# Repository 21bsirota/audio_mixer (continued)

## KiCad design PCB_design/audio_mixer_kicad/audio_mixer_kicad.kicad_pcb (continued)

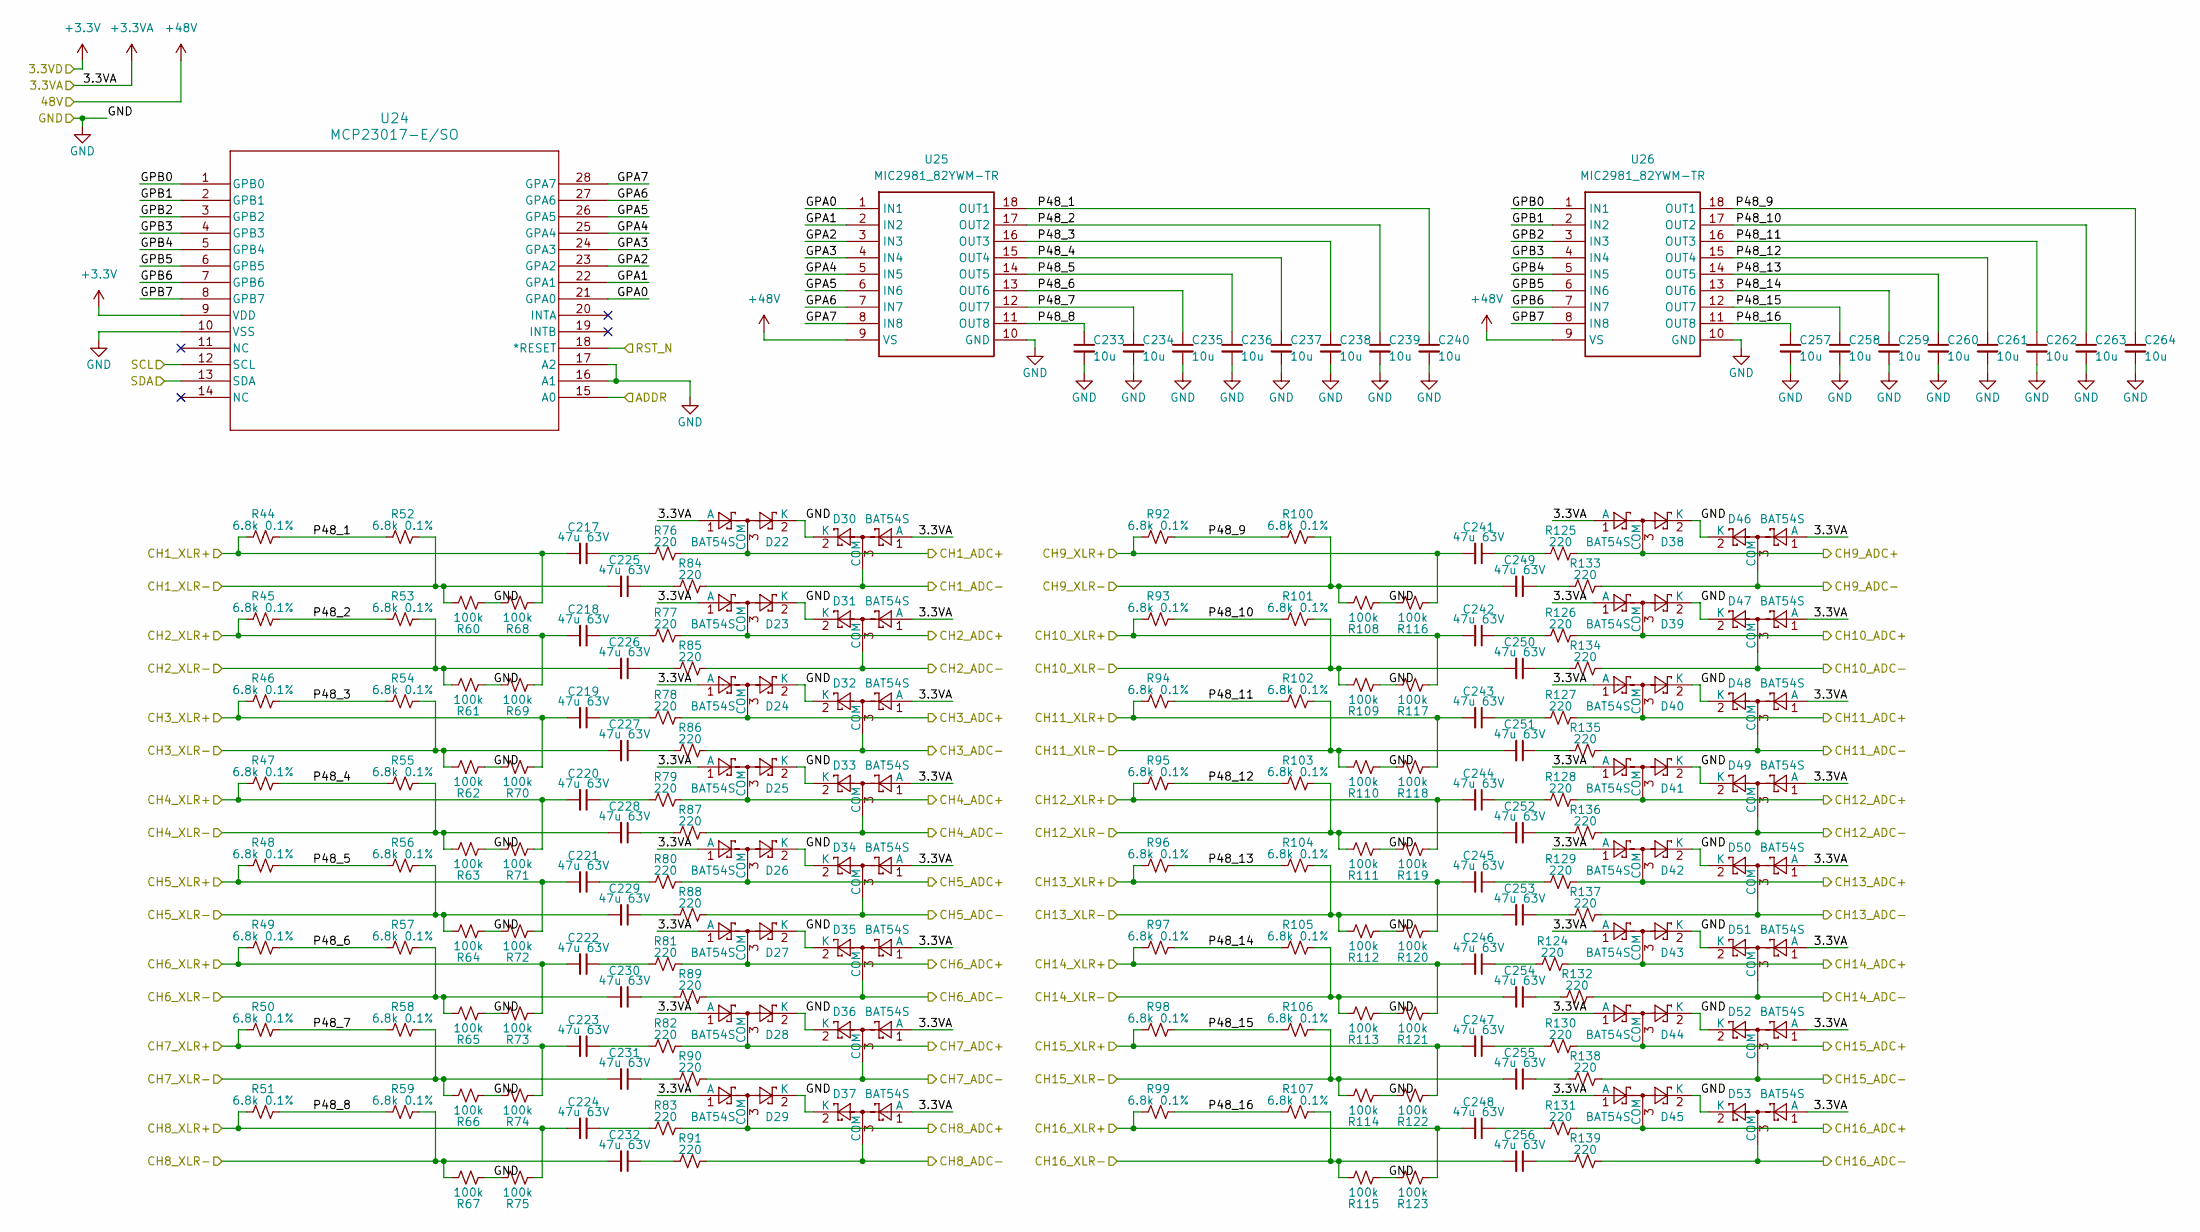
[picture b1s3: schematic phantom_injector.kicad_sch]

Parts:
C217, C218, C219, C220, C221, C222, C223, C224, C225, C226, C227, C228, C229, C230, C231, C232, C241, C242, C243, C244, C245, C246, C247, C248, C249, C250, C251, C252, C253, C254, C255, C256: 47u 63V; C_1206_3216Metric_Pad1.33x1.80mm_HandSolder
C233, C234, C235, C236, C237, C238, C239, C240, C257, C258, C259, C260, C261, C262, C263, C264: 10u; C_1206_3216Metric_Pad1.33x1.80mm_HandSolder
D22, D23, D24, D25, D26, D27, D28, D29, D30, D31, D32, D33, D34, D35, D36, D37, D38, D39, D40, D41, D42, D43, D44, D45, D46, D47, D48, D49, D50, D51, D52, D53: BAT54S; SOT-23
R44, R45, R46, R47, R48, R49, R50, R51, R52, R53, R54, R55, R56, R57, R58, R59, R92, R93, R94, R95, R96, R97, R98, R99, R100, R101, R102, R103, R104, R105, R106, R107: 6.8k 0.1%; R_1206_3216Metric_Pad1.30x1.75mm_HandSolder
R60, R61, R62, R63, R64, R65, R66, R67, R68, R69, R70, R71, R72, R73, R74, R75, R108, R109, R110, R111, R112, R113, R114, R115, R116, R117, R118, R119, R120, R121, R122, R123: 100k; R_1206_3216Metric_Pad1.30x1.75mm_HandSolder
R76, R77, R78, R79, R80, R81, R82, R83, R84, R85, R86, R87, R88, R89, R90, R91, R124, R125, R126, R127, R128, R129, R130, R131, R132, R133, R134, R135, R136, R137, R138, R139: 220; R_1206_3216Metric_Pad1.30x1.75mm_HandSolder
U24: MCP23017-E/SO; SOIC28-W_MC_MCH
U25, U26: MIC2981_82YWM-TR; SOIC127P1031X262-18N; Mouser Part Number 998-MIC2981/82YWMTR

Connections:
+3.3V: U24.9 (VDD); also elsewhere on the board
+3.3VA: D22.1 (A), D23.1 (A), D24.1 (A), D25.1 (A), D26.1 (A), D27.1 (A), D28.1 (A), D29.1 (A), D30.1 (A), D31.1 (A), D32.1 (A), D33.1 (A), D34.1 (A), D35.1 (A), D36.1 (A), D37.1 (A), D38.1 (A), D39.1 (A), D40.1 (A), D41.1 (A), D42.1 (A), D43.1 (A), D44.1 (A), D45.1 (A), D46.1 (A), D47.1 (A), D48.1 (A), D49.1 (A), D50.1 (A), D51.1 (A), D52.1 (A), D53.1 (A); also elsewhere on the board
+48V: U25.9 (VS), U26.9 (VS); also elsewhere on the board
/CH1_ADC+: D22.3 (COM), R76.2; also elsewhere on the board
/CH1_ADC-: D30.3 (COM), R84.2; also elsewhere on the board
/CH1_XLR+: C217.2, R44.1, R68.2; also elsewhere on the board
/CH1_XLR-: C225.2, R52.2, R60.1; also elsewhere on the board
/CH2_ADC+: D23.3 (COM), R77.2; also elsewhere on the board
/CH2_ADC-: D31.3 (COM), R85.2; also elsewhere on the board
/CH2_XLR+: C218.2, R45.1, R69.2; also elsewhere on the board
/CH2_XLR-: C226.2, R53.2, R61.1; also elsewhere on the board
/CH3_ADC+: D24.3 (COM), R78.2; also elsewhere on the board
/CH3_ADC-: D32.3 (COM), R86.2; also elsewhere on the board
/CH3_XLR+: C219.2, R46.1, R70.2; also elsewhere on the board
/CH3_XLR-: C227.2, R54.2, R62.1; also elsewhere on the board
/CH4_ADC+: D25.3 (COM), R79.2; also elsewhere on the board
/CH4_ADC-: D33.3 (COM), R87.2; also elsewhere on the board
/CH4_XLR+: C220.2, R47.1, R71.2; also elsewhere on the board
/CH4_XLR-: C228.2, R55.2, R63.1; also elsewhere on the board
/CH5_ADC+: D26.3 (COM), R80.2; also elsewhere on the board
/CH5_ADC-: D34.3 (COM), R88.2; also elsewhere on the board
/CH5_XLR+: C221.2, R48.1, R72.2; also elsewhere on the board
/CH5_XLR-: C229.2, R56.2, R64.1; also elsewhere on the board
/CH6_ADC+: D27.3 (COM), R81.2; also elsewhere on the board
/CH6_ADC-: D35.3 (COM), R89.2; also elsewhere on the board
/CH6_XLR+: C222.2, R49.1, R73.2; also elsewhere on the board
/CH6_XLR-: C230.2, R57.2, R65.1; also elsewhere on the board
/CH7_ADC+: D28.3 (COM), R82.2; also elsewhere on the board
/CH7_ADC-: D36.3 (COM), R90.2; also elsewhere on the board
/CH7_XLR+: C223.2, R50.1, R74.2; also elsewhere on the board
/CH7_XLR-: C231.2, R58.2, R66.1; also elsewhere on the board
/CH8_ADC+: D29.3 (COM), R83.2; also elsewhere on the board
/CH8_ADC-: D37.3 (COM), R91.2; also elsewhere on the board
/CH8_XLR+: C224.2, R51.1, R75.2; also elsewhere on the board
/CH8_XLR-: C232.2, R59.2, R67.1; also elsewhere on the board
/CH9_ADC+: D38.3 (COM), R125.2; also elsewhere on the board
/CH9_ADC-: D46.3 (COM), R133.2; also elsewhere on the board
/CH9_XLR+: C241.2, R92.1, R116.2; also elsewhere on the board
/CH9_XLR-: C249.2, R100.2, R108.1; also elsewhere on the board
/CH10_ADC+: D39.3 (COM), R126.2; also elsewhere on the board
/CH10_ADC-: D47.3 (COM), R134.2; also elsewhere on the board
/CH10_XLR+: C242.2, R93.1, R117.2; also elsewhere on the board
/CH10_XLR-: C250.2, R101.2, R109.1; also elsewhere on the board
/CH11_ADC+: D40.3 (COM), R127.2; also elsewhere on the board
/CH11_ADC-: D48.3 (COM), R135.2; also elsewhere on the board
/CH11_XLR+: C243.2, R94.1, R118.2; also elsewhere on the board
/CH11_XLR-: C251.2, R102.2, R110.1; also elsewhere on the board
/CH12_ADC+: D41.3 (COM), R128.2; also elsewhere on the board
/CH12_ADC-: D49.3 (COM), R136.2; also elsewhere on the board
/CH12_XLR+: C244.2, R95.1, R119.2; also elsewhere on the board
/CH12_XLR-: C252.2, R103.2, R111.1; also elsewhere on the board
/CH13_ADC+: D42.3 (COM), R129.2; also elsewhere on the board
/CH13_ADC-: D50.3 (COM), R137.2; also elsewhere on the board
/CH13_XLR+: C245.2, R96.1, R120.2; also elsewhere on the board
/CH13_XLR-: C253.2, R104.2, R112.1; also elsewhere on the board
/CH14_ADC+: D43.3 (COM), R124.2; also elsewhere on the board
/CH14_ADC-: D51.3 (COM), R132.2; also elsewhere on the board
/CH14_XLR+: C246.2, R97.1, R121.2; also elsewhere on the board
/CH14_XLR-: C254.2, R105.2, R113.1; also elsewhere on the board
/CH15_ADC+: D44.3 (COM), R130.2; also elsewhere on the board
/CH15_ADC-: D52.3 (COM), R138.2; also elsewhere on the board
/CH15_XLR+: C247.2, R98.1, R122.2; also elsewhere on the board
/CH15_XLR-: C255.2, R106.2, R114.1; also elsewhere on the board
/CH16_ADC+: D45.3 (COM), R131.2; also elsewhere on the board
/CH16_ADC-: D53.3 (COM), R139.2; also elsewhere on the board
/CH16_XLR+: C248.2, R99.1, R123.2; also elsewhere on the board
/CH16_XLR-: C256.2, R107.2, R115.1; also elsewhere on the board
/I2C1_SCL: U24.12 (SCL); also elsewhere on the board
/I2C1_SDA: U24.13 (SDA); also elsewhere on the board
/Phantom Injector 0/GPA0: U24.21 (GPA0), U25.1 (IN1)
/Phantom Injector 0/GPA1: U24.22 (GPA1), U25.2 (IN2)
/Phantom Injector 0/GPA2: U24.23 (GPA2), U25.3 (IN3)
/Phantom Injector 0/GPA3: U24.24 (GPA3), U25.4 (IN4)
/Phantom Injector 0/GPA4: U24.25 (GPA4), U25.5 (IN5)
/Phantom Injector 0/GPA5: U24.26 (GPA5), U25.6 (IN6)
/Phantom Injector 0/GPA6: U24.27 (GPA6), U25.7 (IN7)
/Phantom Injector 0/GPA7: U24.28 (GPA7), U25.8 (IN8)
/Phantom Injector 0/GPB0: U24.1 (GPB0), U26.1 (IN1)
/Phantom Injector 0/GPB1: U24.2 (GPB1), U26.2 (IN2)
/Phantom Injector 0/GPB2: U24.3 (GPB2), U26.3 (IN3)
/Phantom Injector 0/GPB3: U24.4 (GPB3), U26.4 (IN4)
/Phantom Injector 0/GPB4: U24.5 (GPB4), U26.5 (IN5)
/Phantom Injector 0/GPB5: U24.6 (GPB5), U26.6 (IN6)
/Phantom Injector 0/GPB6: U24.7 (GPB6), U26.7 (IN7)
/Phantom Injector 0/GPB7: U24.8 (GPB7), U26.8 (IN8)
/Phantom Injector 0/P48_1: C240.1, R44.2, R52.1, U25.18 (OUT1)
/Phantom Injector 0/P48_2: C239.1, R45.2, R53.1, U25.17 (OUT2)
/Phantom Injector 0/P48_3: C238.1, R46.2, R54.1, U25.16 (OUT3)
/Phantom Injector 0/P48_4: C237.1, R47.2, R55.1, U25.15 (OUT4)
/Phantom Injector 0/P48_5: C236.1, R48.2, R56.1, U25.14 (OUT5)
/Phantom Injector 0/P48_6: C235.1, R49.2, R57.1, U25.13 (OUT6)
/Phantom Injector 0/P48_7: C234.1, R50.2, R58.1, U25.12 (OUT7)
/Phantom Injector 0/P48_8: C233.1, R51.2, R59.1, U25.11 (OUT8)
/Phantom Injector 0/P48_9: C264.1, R92.2, R100.1, U26.18 (OUT1)
/Phantom Injector 0/P48_10: C263.1, R93.2, R101.1, U26.17 (OUT2)
/Phantom Injector 0/P48_11: C262.1, R94.2, R102.1, U26.16 (OUT3)
/Phantom Injector 0/P48_12: C261.1, R95.2, R103.1, U26.15 (OUT4)
/Phantom Injector 0/P48_13: C260.1, R96.2, R104.1, U26.14 (OUT5)
/Phantom Injector 0/P48_14: C259.1, R97.2, R105.1, U26.13 (OUT6)
/Phantom Injector 0/P48_15: C258.1, R98.2, R106.1, U26.12 (OUT7)
/Phantom Injector 0/P48_16: C257.1, R99.2, R107.1, U26.11 (OUT8)
/RST_N: U24.18 (*RESET); also elsewhere on the board
GND: C233.2, C234.2, C235.2, C236.2, C237.2, C238.2, C239.2, C240.2, C257.2, C258.2, C259.2, C260.2, C261.2, C262.2, C263.2, C264.2, D22.2 (K), D23.2 (K), D24.2 (K), D25.2 (K), D26.2 (K), D27.2 (K), D28.2 (K), D29.2 (K), D30.2 (K), D31.2 (K), D32.2 (K), D33.2 (K), D34.2 (K), D35.2 (K), D36.2 (K), D37.2 (K), D38.2 (K), D39.2 (K), D40.2 (K), D41.2 (K), D42.2 (K), D43.2 (K), D44.2 (K), D45.2 (K), D46.2 (K), D47.2 (K), D48.2 (K), D49.2 (K), D50.2 (K), D51.2 (K), D52.2 (K), D53.2 (K), R60.2, R61.2, R62.2, R63.2, R64.2, R65.2, R66.2, R67.2, R68.1, R69.1, R70.1, R71.1, R72.1, R73.1, R74.1, R75.1, R108.2, R109.2, R110.2, R111.2, R112.2, R113.2, R114.2, R115.2, R116.1, R117.1, R118.1, R119.1, R120.1, R121.1, R122.1, R123.1, U24.10 (VSS), U24.15 (A0), U24.16 (A1), U24.17 (A2), U25.10 (GND), U26.10 (GND); also elsewhere on the board
unnamed: C217.1, R76.1
unnamed: C218.1, R77.1
unnamed: C219.1, R78.1
unnamed: C220.1, R79.1
unnamed: C221.1, R80.1
unnamed: C222.1, R81.1
unnamed: C223.1, R82.1
unnamed: C224.1, R83.1
unnamed: C225.1, R84.1
unnamed: C226.1, R85.1
unnamed: C227.1, R86.1
unnamed: C228.1, R87.1
unnamed: C229.1, R88.1
unnamed: C230.1, R89.1
unnamed: C231.1, R90.1
unnamed: C232.1, R91.1
unnamed: C241.1, R125.1
unnamed: C242.1, R126.1
unnamed: C243.1, R127.1
unnamed: C244.1, R128.1
unnamed: C245.1, R129.1
unnamed: C246.1, R124.1
unnamed: C247.1, R130.1
unnamed: C248.1, R131.1
unnamed: C249.1, R133.1
unnamed: C250.1, R134.1
unnamed: C251.1, R135.1
unnamed: C252.1, R136.1
unnamed: C253.1, R137.1
unnamed: C254.1, R132.1
unnamed: C255.1, R138.1
unnamed: C256.1, R139.1

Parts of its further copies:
C265, C266, C267, C268, C269, C270, C271, C272, C273, C274, C275, C276, C277, C278, C279, C280, C289, C290, C291, C292, C293, C294, C295, C296, C297, C298, C299, C300, C301, C302, C303, C304: 47u 63V; C_1206_3216Metric_Pad1.33x1.80mm_HandSolder
C281, C282, C283, C284, C285, C286, C287, C288, C305, C306, C307, C308, C309, C310, C311, C312: 10u; C_1206_3216Metric_Pad1.33x1.80mm_HandSolder
D54, D55, D56, D57, D58, D59, D60, D61, D62, D63, D64, D65, D66, D67, D68, D69, D70, D71, D72, D73, D74, D75, D76, D77, D78, D79, D80, D81, D82, D83, D84, D85: BAT54S; SOT-23
R140, R141, R142, R143, R144, R145, R146, R147, R148, R149, R150, R151, R152, R153, R154, R155, R188, R189, R190, R191, R192, R193, R194, R195, R196, R197, R198, R199, R200, R201, R202, R203: 6.8k 0.1%; R_1206_3216Metric_Pad1.30x1.75mm_HandSolder
R156, R157, R158, R159, R160, R161, R162, R163, R164, R165, R166, R167, R168, R169, R170, R171, R204, R205, R206, R207, R208, R209, R210, R211, R212, R213, R214, R215, R216, R217, R218, R219: 100k; R_1206_3216Metric_Pad1.30x1.75mm_HandSolder
R172, R173, R174, R175, R176, R177, R178, R179, R180, R181, R182, R183, R184, R185, R186, R187, R220, R221, R222, R223, R224, R225, R226, R227, R228, R229, R230, R231, R232, R233, R234, R235: 220; R_1206_3216Metric_Pad1.30x1.75mm_HandSolder
U27: MCP23017-E/SO; SOIC28-W_MC_MCH
U28, U29: MIC2981_82YWM-TR; SOIC127P1031X262-18N; Mouser Part Number 998-MIC2981/82YWMTR

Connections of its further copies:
+3.3V: U27.9 (VDD), U27.15 (A0); also elsewhere on the board
+3.3VA: D54.1 (A), D55.1 (A), D56.1 (A), D57.1 (A), D58.1 (A), D59.1 (A), D60.1 (A), D61.1 (A), D62.1 (A), D63.1 (A), D64.1 (A), D65.1 (A), D66.1 (A), D67.1 (A), D68.1 (A), D69.1 (A), D70.1 (A), D71.1 (A), D72.1 (A), D73.1 (A), D74.1 (A), D75.1 (A), D76.1 (A), D77.1 (A), D78.1 (A), D79.1 (A), D80.1 (A), D81.1 (A), D82.1 (A), D83.1 (A), D84.1 (A), D85.1 (A); also elsewhere on the board
+48V: U28.9 (VS), U29.9 (VS); also elsewhere on the board
/CH17_ADC+: D54.3 (COM), R172.2; also elsewhere on the board
/CH17_ADC-: D62.3 (COM), R180.2; also elsewhere on the board
/CH17_XLR+: C265.2, R140.1, R164.2; also elsewhere on the board
/CH17_XLR-: C273.2, R148.2, R156.1; also elsewhere on the board
/CH18_ADC+: D55.3 (COM), R173.2; also elsewhere on the board
/CH18_ADC-: D63.3 (COM), R181.2; also elsewhere on the board
/CH18_XLR+: C266.2, R141.1, R165.2; also elsewhere on the board
/CH18_XLR-: C274.2, R149.2, R157.1; also elsewhere on the board
/CH19_ADC+: D56.3 (COM), R174.2; also elsewhere on the board
/CH19_ADC-: D64.3 (COM), R182.2; also elsewhere on the board
/CH19_XLR+: C267.2, R142.1, R166.2; also elsewhere on the board
/CH19_XLR-: C275.2, R150.2, R158.1; also elsewhere on the board
/CH20_ADC+: D57.3 (COM), R175.2; also elsewhere on the board
/CH20_ADC-: D65.3 (COM), R183.2; also elsewhere on the board
/CH20_XLR+: C268.2, R143.1, R167.2; also elsewhere on the board
/CH20_XLR-: C276.2, R151.2, R159.1; also elsewhere on the board
/CH21_ADC+: D58.3 (COM), R176.2; also elsewhere on the board
/CH21_ADC-: D66.3 (COM), R184.2; also elsewhere on the board
/CH21_XLR+: C269.2, R144.1, R168.2; also elsewhere on the board
/CH21_XLR-: C277.2, R152.2, R160.1; also elsewhere on the board
/CH22_ADC+: D59.3 (COM), R177.2; also elsewhere on the board
/CH22_ADC-: D67.3 (COM), R185.2; also elsewhere on the board
/CH22_XLR+: C270.2, R145.1, R169.2; also elsewhere on the board
/CH22_XLR-: C278.2, R153.2, R161.1; also elsewhere on the board
/CH23_ADC+: D60.3 (COM), R178.2; also elsewhere on the board
/CH23_ADC-: D68.3 (COM), R186.2; also elsewhere on the board
/CH23_XLR+: C271.2, R146.1, R170.2; also elsewhere on the board
/CH23_XLR-: C279.2, R154.2, R162.1; also elsewhere on the board
/CH24_ADC+: D61.3 (COM), R179.2; also elsewhere on the board
/CH24_ADC-: D69.3 (COM), R187.2; also elsewhere on the board
/CH24_XLR+: C272.2, R147.1, R171.2; also elsewhere on the board
/CH24_XLR-: C280.2, R155.2, R163.1; also elsewhere on the board
/CH25_ADC+: D70.3 (COM), R221.2; also elsewhere on the board
/CH25_ADC-: D78.3 (COM), R229.2; also elsewhere on the board
/CH25_XLR+: C289.2, R188.1, R212.2; also elsewhere on the board
/CH25_XLR-: C297.2, R196.2, R204.1; also elsewhere on the board
/CH26_ADC+: D71.3 (COM), R222.2; also elsewhere on the board
/CH26_ADC-: D79.3 (COM), R230.2; also elsewhere on the board
/CH26_XLR+: C290.2, R189.1, R213.2; also elsewhere on the board
/CH26_XLR-: C298.2, R197.2, R205.1; also elsewhere on the board
/CH27_ADC+: D72.3 (COM), R223.2; also elsewhere on the board
/CH27_ADC-: D80.3 (COM), R231.2; also elsewhere on the board
/CH27_XLR+: C291.2, R190.1, R214.2; also elsewhere on the board
/CH27_XLR-: C299.2, R198.2, R206.1; also elsewhere on the board
/CH28_ADC+: D73.3 (COM), R224.2; also elsewhere on the board
/CH28_ADC-: D81.3 (COM), R232.2; also elsewhere on the board
/CH28_XLR+: C292.2, R191.1, R215.2; also elsewhere on the board
/CH28_XLR-: C300.2, R199.2, R207.1; also elsewhere on the board
/CH29_ADC+: D74.3 (COM), R225.2; also elsewhere on the board
/CH29_ADC-: D82.3 (COM), R233.2; also elsewhere on the board
/CH29_XLR+: C293.2, R192.1, R216.2; also elsewhere on the board
/CH29_XLR-: C301.2, R200.2, R208.1; also elsewhere on the board
/CH30_ADC+: D75.3 (COM), R220.2; also elsewhere on the board
/CH30_ADC-: D83.3 (COM), R228.2; also elsewhere on the board
/CH30_XLR+: C294.2, R193.1, R217.2; also elsewhere on the board
/CH30_XLR-: C302.2, R201.2, R209.1; also elsewhere on the board
/CH31_ADC+: D76.3 (COM), R226.2; also elsewhere on the board
/CH31_ADC-: D84.3 (COM), R234.2; also elsewhere on the board
/CH31_XLR+: C295.2, R194.1, R218.2; also elsewhere on the board
/CH31_XLR-: C303.2, R202.2, R210.1; also elsewhere on the board
/CH32_ADC+: D77.3 (COM), R227.2; also elsewhere on the board
/CH32_ADC-: D85.3 (COM), R235.2; also elsewhere on the board
/CH32_XLR+: C296.2, R195.1, R219.2; also elsewhere on the board
/CH32_XLR-: C304.2, R203.2, R211.1; also elsewhere on the board
/I2C0_SCL: U27.12 (SCL); also elsewhere on the board
/I2C0_SDA: U27.13 (SDA); also elsewhere on the board
/Phantom Injector 1/GPA0: U27.21 (GPA0), U28.1 (IN1)
/Phantom Injector 1/GPA1: U27.22 (GPA1), U28.2 (IN2)
/Phantom Injector 1/GPA2: U27.23 (GPA2), U28.3 (IN3)
/Phantom Injector 1/GPA3: U27.24 (GPA3), U28.4 (IN4)
/Phantom Injector 1/GPA4: U27.25 (GPA4), U28.5 (IN5)
/Phantom Injector 1/GPA5: U27.26 (GPA5), U28.6 (IN6)
/Phantom Injector 1/GPA6: U27.27 (GPA6), U28.7 (IN7)
/Phantom Injector 1/GPA7: U27.28 (GPA7), U28.8 (IN8)
/Phantom Injector 1/GPB0: U27.1 (GPB0), U29.1 (IN1)
/Phantom Injector 1/GPB1: U27.2 (GPB1), U29.2 (IN2)
/Phantom Injector 1/GPB2: U27.3 (GPB2), U29.3 (IN3)
/Phantom Injector 1/GPB3: U27.4 (GPB3), U29.4 (IN4)
/Phantom Injector 1/GPB4: U27.5 (GPB4), U29.5 (IN5)
/Phantom Injector 1/GPB5: U27.6 (GPB5), U29.6 (IN6)
/Phantom Injector 1/GPB6: U27.7 (GPB6), U29.7 (IN7)
/Phantom Injector 1/GPB7: U27.8 (GPB7), U29.8 (IN8)
/Phantom Injector 1/P48_1: C288.1, R140.2, R148.1, U28.18 (OUT1)
/Phantom Injector 1/P48_2: C287.1, R141.2, R149.1, U28.17 (OUT2)
/Phantom Injector 1/P48_3: C286.1, R142.2, R150.1, U28.16 (OUT3)
/Phantom Injector 1/P48_4: C285.1, R143.2, R151.1, U28.15 (OUT4)
/Phantom Injector 1/P48_5: C284.1, R144.2, R152.1, U28.14 (OUT5)
/Phantom Injector 1/P48_6: C283.1, R145.2, R153.1, U28.13 (OUT6)
/Phantom Injector 1/P48_7: C282.1, R146.2, R154.1, U28.12 (OUT7)
/Phantom Injector 1/P48_8: C281.1, R147.2, R155.1, U28.11 (OUT8)
/Phantom Injector 1/P48_9: C312.1, R188.2, R196.1, U29.18 (OUT1)
/Phantom Injector 1/P48_10: C311.1, R189.2, R197.1, U29.17 (OUT2)
/Phantom Injector 1/P48_11: C310.1, R190.2, R198.1, U29.16 (OUT3)
/Phantom Injector 1/P48_12: C309.1, R191.2, R199.1, U29.15 (OUT4)
/Phantom Injector 1/P48_13: C308.1, R192.2, R200.1, U29.14 (OUT5)
/Phantom Injector 1/P48_14: C307.1, R193.2, R201.1, U29.13 (OUT6)
/Phantom Injector 1/P48_15: C306.1, R194.2, R202.1, U29.12 (OUT7)
/Phantom Injector 1/P48_16: C305.1, R195.2, R203.1, U29.11 (OUT8)
/RST_N: U27.18 (*RESET); also elsewhere on the board
GND: C281.2, C282.2, C283.2, C284.2, C285.2, C286.2, C287.2, C288.2, C305.2, C306.2, C307.2, C308.2, C309.2, C310.2, C311.2, C312.2, D54.2 (K), D55.2 (K), D56.2 (K), D57.2 (K), D58.2 (K), D59.2 (K), D60.2 (K), D61.2 (K), D62.2 (K), D63.2 (K), D64.2 (K), D65.2 (K), D66.2 (K), D67.2 (K), D68.2 (K), D69.2 (K), D70.2 (K), D71.2 (K), D72.2 (K), D73.2 (K), D74.2 (K), D75.2 (K), D76.2 (K), D77.2 (K), D78.2 (K), D79.2 (K), D80.2 (K), D81.2 (K), D82.2 (K), D83.2 (K), D84.2 (K), D85.2 (K), R156.2, R157.2, R158.2, R159.2, R160.2, R161.2, R162.2, R163.2, R164.1, R165.1, R166.1, R167.1, R168.1, R169.1, R170.1, R171.1, R204.2, R205.2, R206.2, R207.2, R208.2, R209.2, R210.2, R211.2, R212.1, R213.1, R214.1, R215.1, R216.1, R217.1, R218.1, R219.1, U27.10 (VSS), U27.16 (A1), U27.17 (A2), U28.10 (GND), U29.10 (GND); also elsewhere on the board
unnamed: C265.1, R172.1
unnamed: C266.1, R173.1
unnamed: C267.1, R174.1
unnamed: C268.1, R175.1
unnamed: C269.1, R176.1
unnamed: C270.1, R177.1
unnamed: C271.1, R178.1
unnamed: C272.1, R179.1
unnamed: C273.1, R180.1
unnamed: C274.1, R181.1
unnamed: C275.1, R182.1
unnamed: C276.1, R183.1
unnamed: C277.1, R184.1
unnamed: C278.1, R185.1
unnamed: C279.1, R186.1
unnamed: C280.1, R187.1
unnamed: C289.1, R221.1
unnamed: C290.1, R222.1
unnamed: C291.1, R223.1
unnamed: C292.1, R224.1
unnamed: C293.1, R225.1
unnamed: C294.1, R220.1
unnamed: C295.1, R226.1
unnamed: C296.1, R227.1
unnamed: C297.1, R229.1
unnamed: C298.1, R230.1
unnamed: C299.1, R231.1
unnamed: C300.1, R232.1
unnamed: C301.1, R233.1
unnamed: C302.1, R228.1
unnamed: C303.1, R234.1
unnamed: C304.1, R235.1

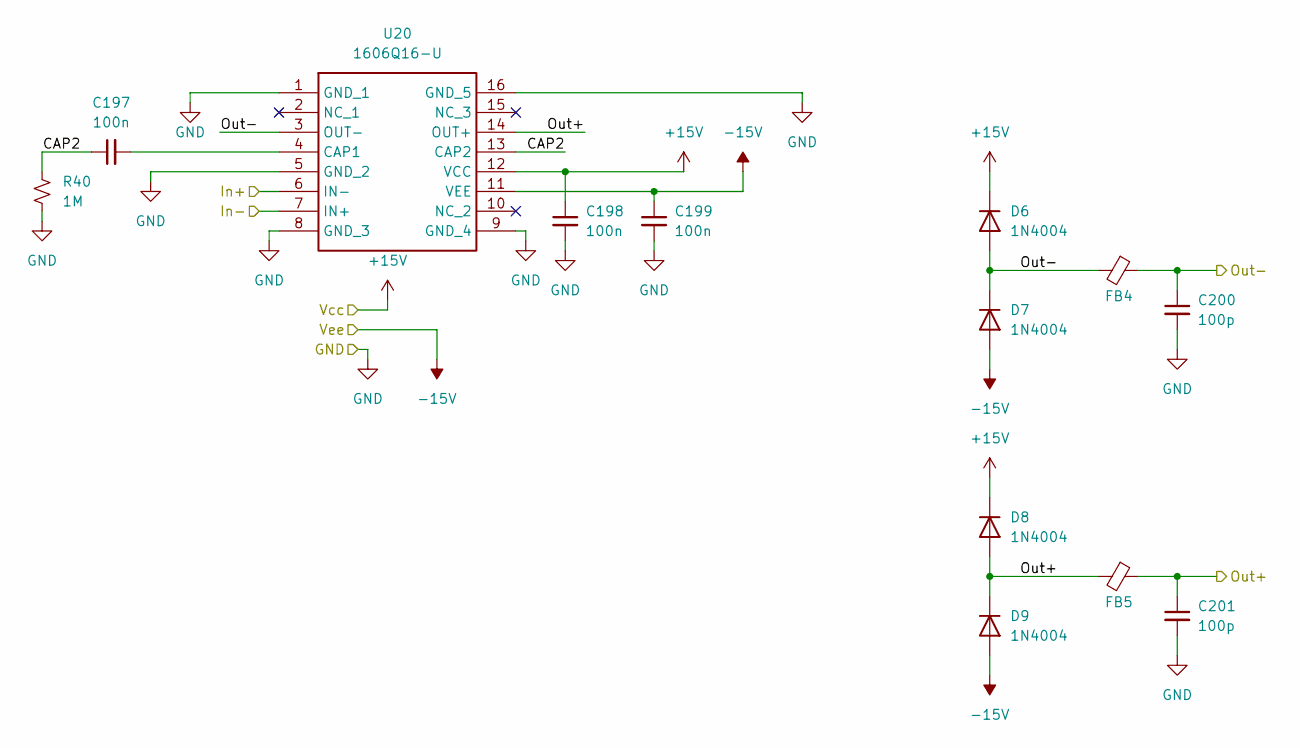
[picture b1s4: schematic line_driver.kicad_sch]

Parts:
C197, C198, C199: 100n; C_1206_3216Metric_Pad1.33x1.80mm_HandSolder
C200, C201: 100p; C_1206_3216Metric_Pad1.33x1.80mm_HandSolder
D6, D7, D8, D9: 1N4004; D_DO-41_SOD81_P10.16mm_Horizontal
FB4, FB5: FerriteBead_Small; L_1206_3216Metric_Pad1.22x1.90mm_HandSolder
R40: 1M; R_1206_3216Metric_Pad1.30x1.75mm_HandSolder
U20: 1606Q16-U; SOP64P600X175-16N; Mouser Part Number 887-1606Q16-U

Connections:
+15V: C198.1, D6.1 (K), D8.1 (K), U20.12 (VCC); also elsewhere on the board
-15V: C199.1, D7.2 (A), D9.2 (A), U20.11 (VEE); also elsewhere on the board
/DAC0/OUT1M: U20.7 (IN+); also elsewhere on the board
/DAC0/OUT1P: U20.6 (IN-); also elsewhere on the board
/LD0/CAP2: C197.1, R40.2, U20.13 (CAP2)
/LD0/Out+: C201.1, D8.2 (A), D9.1 (K), FB5.1, FB5.2, U20.14 (OUT+); also elsewhere on the board
/LD0/Out-: C200.1, D6.2 (A), D7.1 (K), FB4.1, FB4.2, U20.3 (OUT-); also elsewhere on the board
GND: C198.2, C199.2, C200.2, C201.2, R40.1, U20.1 (GND_1), U20.5 (GND_2), U20.8 (GND_3), U20.9 (GND_4), U20.16 (GND_5); also elsewhere on the board
unnamed: C197.2, U20.4 (CAP1)

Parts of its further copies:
C202, C203, C204, C207, C208, C209, C212, C213, C214: 100n; C_1206_3216Metric_Pad1.33x1.80mm_HandSolder
C205, C206, C210, C211, C215, C216: 100p; C_1206_3216Metric_Pad1.33x1.80mm_HandSolder
D10, D11, D12, D13, D14, D15, D16, D17, D18, D19, D20, D21: 1N4004; D_DO-41_SOD81_P10.16mm_Horizontal
FB6, FB7, FB8, FB9, FB10, FB11: FerriteBead_Small; L_1206_3216Metric_Pad1.22x1.90mm_HandSolder
R41, R42, R43: 1M; R_1206_3216Metric_Pad1.30x1.75mm_HandSolder
U21, U22, U23: 1606Q16-U; SOP64P600X175-16N; Mouser Part Number 887-1606Q16-U

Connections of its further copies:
+15V: C203.1, C208.1, C213.1, D10.1 (K), D12.1 (K), D14.1 (K), D16.1 (K), D18.1 (K), D20.1 (K), U21.12 (VCC), U22.12 (VCC), U23.12 (VCC); also elsewhere on the board
-15V: C204.1, C209.1, C214.1, D11.2 (A), D13.2 (A), D15.2 (A), D17.2 (A), D19.2 (A), D21.2 (A), U21.11 (VEE), U22.11 (VEE), U23.11 (VEE); also elsewhere on the board
/DAC0/OUT2M: U21.7 (IN+); also elsewhere on the board
/DAC0/OUT2P: U21.6 (IN-); also elsewhere on the board
/DAC1/OUT1M: U22.7 (IN+); also elsewhere on the board
/DAC1/OUT1P: U22.6 (IN-); also elsewhere on the board
/DAC1/OUT2M: U23.7 (IN+); also elsewhere on the board
/DAC1/OUT2P: U23.6 (IN-); also elsewhere on the board
/LD1/CAP2: C202.1, R41.2, U21.13 (CAP2)
/LD1/Out+: C206.1, D12.2 (A), D13.1 (K), FB7.1, FB7.2, U21.14 (OUT+); also elsewhere on the board
/LD1/Out-: C205.1, D10.2 (A), D11.1 (K), FB6.1, FB6.2, U21.3 (OUT-); also elsewhere on the board
/LD2/CAP2: C207.1, R42.2, U22.13 (CAP2)
/LD2/Out+: C211.1, D16.2 (A), D17.1 (K), FB9.1, FB9.2, U22.14 (OUT+); also elsewhere on the board
/LD2/Out-: C210.1, D14.2 (A), D15.1 (K), FB8.1, FB8.2, U22.3 (OUT-); also elsewhere on the board
/LD3/CAP2: C212.1, R43.2, U23.13 (CAP2)
/LD3/Out+: C216.1, D20.2 (A), D21.1 (K), FB11.1, FB11.2, U23.14 (OUT+); also elsewhere on the board
/LD3/Out-: C215.1, D18.2 (A), D19.1 (K), FB10.1, FB10.2, U23.3 (OUT-); also elsewhere on the board
GND: C203.2, C204.2, C205.2, C206.2, C208.2, C209.2, C210.2, C211.2, C213.2, C214.2, C215.2, C216.2, R41.1, R42.1, R43.1, U21.1 (GND_1), U21.5 (GND_2), U21.8 (GND_3), U21.9 (GND_4), U21.16 (GND_5), U22.1 (GND_1), U22.5 (GND_2), U22.8 (GND_3), U22.9 (GND_4), U22.16 (GND_5), U23.1 (GND_1), U23.5 (GND_2), U23.8 (GND_3), U23.9 (GND_4), U23.16 (GND_5); also elsewhere on the board
unnamed: C202.2, U21.4 (CAP1)
unnamed: C207.2, U22.4 (CAP1)
unnamed: C212.2, U23.4 (CAP1)
